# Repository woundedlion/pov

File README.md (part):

# Holosphere

[▶ Play with the live WebAssembly simulator](https://woundedlion.github.io/daydream/)

[📖 API documentation (Doxygen)](https://woundedlion.github.io/pov/)

---

<p align="center">
  
</p>

Holosphere is a persistence-of-vision (POV) LED sphere and its real-time simulator. The device spins a strip of LEDs at 480 RPM while Teensy microcontrollers fire pixels at microsecond intervals, painting full-color imagery onto the surface of a virtual sphere. The simulator compiles the same C++ effects to WebAssembly and renders them in a browser.

The project spans **two repositories** that ship as one product:

| Repo | Role | What lives here |
|---|---|---|
| [**Holosphere**](https://github.com/woundedlion/pov) | C++ engine + firmware | All rendering code, effects, hardware drivers (`pov_single.h`, `pov_segmented.h`), the Emscripten/WASM target, unit tests, and this README. |
| [**daydream**](https://github.com/woundedlion/daydream) | Web simulator | Three.js renderer, GUI and sidebar, recorder, segmented-POV Web Workers, standalone design tools, and the installed `generated/holosphere_wasm.{js,wasm}` engine build. |

Holosphere's WASM install step writes the engine module and everything the simulator mirrors from this repository into a sibling `daydream/` checkout ([§8.2](#82-wasm-build)). The live demo is daydream served from GitHub Pages.

---

## Quickstart

To explore effects, open the [live simulator](https://woundedlion.github.io/daydream/).

For local development:

1. Clone Holosphere and daydream as sibling directories.
2. Install Python with pip, Node.js with npm, CMake, Ninja and Emscripten. The tested tool versions are pinned in `tools/build_pins.py`, and each repository's `package.json` declares its Node requirement. Install the pinned host development tools with pip (including CMake and `just`):

   ```bash
   python -m pip install --require-hashes -r requirements/dev.txt
   ```

3. Install Emscripten in the sibling `../emsdk` checkout (or set `EMSDK` to its location), then build and install the engine from Holosphere:

   ```bash
   just install
   ```

4. In daydream, run `npm ci`, then `python -m http.server 8000 --bind 127.0.0.1`, and open <http://localhost:8000>.

**Troubleshooting.** The WASM recipes load the Emscripten environment automatically; check `EMSDK` if your SDK lives outside `../emsdk`. If daydream's provenance test reports a bundle mismatch, rerun `just install` to refresh the engine and its provenance together. Documentation checks need the daydream checkout at the revision pinned in `tools/build_pins.py`.

[§8 Building and Testing](#8-building-and-testing) covers native tests, firmware uploads and CI.

## Table of Contents

1. [Hardware](#1-hardware)
2. [Architecture](#2-architecture)
3. [Design Decisions](#3-design-decisions)
4. [Frame Lifecycle](#4-frame-lifecycle)
5. [Rendering](#5-rendering)
   - [5.1 Rendering Paths at a Glance](#51-rendering-paths-at-a-glance)
   - [5.2 Shared Building Blocks](#52-shared-building-blocks)
   - [5.3 Forward Rendering: Scan](#53-forward-rendering-scan)
   - [5.4 Forward Rendering: Plot](#54-forward-rendering-plot)
   - [5.5 Full-Screen Shading](#55-full-screen-shading)
   - [5.6 Pullback Shading](#56-pullback-shading)
   - [5.7 Raycasting and Raymarching](#57-raycasting-and-raymarching)
   - [5.8 The Filter Pipeline](#58-the-filter-pipeline)
6. [Effects](#6-effects)
7. [The Web Simulator (Daydream)](#7-the-web-simulator-daydream)
8. [Building and Testing](#8-building-and-testing)
9. [Repository Map](#9-repository-map)

- [License](#license)

---

## 1. Hardware

Two physical targets share the same rendering engine.

### 1.1 Holosphere (2015)

| Component | Detail |
|---|---|
| Controller | Teensy 4.0 (600 MHz ARM Cortex-M7) |
| LEDs | 40-pixel addressable strip (20 per half-arm, two-arm rotation) |
| Protocol | SPI via FastLED (WS2801 at 6 MHz) or DMA (HD107S at 12 MHz) |
| Rotation | 480 RPM (8 revolutions/second) |
| Virtual resolution | 96 × 20 |
| Driver | `POVDisplay<40, 480>` in `pov_single.h` |
| Pin assignments | DATA: pin 11, CLOCK: pin 13, RANDOM seed pin 15: legacy effects only |

### 1.2 Phantasm

| Component | Detail |
|---|---|
| Controllers | 4× Teensy 4.0 by default; optional 8× firmware profile (600 MHz ARM Cortex-M7) |
| LEDs | 288 total: 72 per segment at N=4, 36 per segment at N=8 |
| Protocol | DMA (HD107S at 24 MHz) |
| Rotation | 480 RPM (8 revolutions/second), 16 FPS from 2 sides of the ring |
| Virtual resolution | 288 × 144 |
| Driver | `POVSegmented<288, N, 480>` in `pov_segmented.h`, `N ∈ {4, 8}` (even power of two; `N=2` exceeds the per-column DMA budget at 288 px/480 RPM) |
| Synchronization | 1-wire: count-coded sync symbols from segment 0 discipline a per-board flywheel timebase (`hardware/pov_sync.h`) |
| Pin assignments | ID: pins 21–22 at N=4, plus pin 23 at N=8; Sync: rev 1.1 pin 3 (shared — master drives, downstream receive); rev 1.2 TX pin 4 via U1 (held LOW on downstream boards), RX pin 3, master-enable: pin 5, SPI: pins 11 + 13 |

### 1.3 How the Image Forms

Each revolution takes about 125 ms. The LED strip is mounted on both sides of a rotating arm: the top half of the strip paints one hemisphere and the bottom half paints the opposite one, and the two arms sit half a turn apart in azimuth. Half a revolution therefore paints a complete sphere, and each revolution delivers two frames — one per side.

A new column is painted every `1,000,000 / (RPM/60) / W` microseconds — about 1302 µs for Holosphere's 96 columns and 434 µs for Phantasm's 288. On Holosphere an IntervalTimer ISR advances one column per fire; on Phantasm each board's flywheel ISR derives the column from the CPU cycle counter ([Hardware Drivers](https://github.com/woundedlion/pov/blob/master/docs/subsystems.md#hardware-drivers-dma_ledh-pov_singleh-pov_segmentedh)).

---

## 2. Architecture

### 2.1 Layers

Firmware, WebAssembly and native test targets share one engine:

```text
C++ codebase
  effects/ (46 visual algorithms) + workbench/
              |
  core/                       Rendering engine
    scan / plot -> filter pipeline -> Canvas pixel buffer
    pullback / raycast -> Scan::Shader -> Canvas pixel buffer
              |
  targets/                    Build entry points
    Holosphere/ + Phantasm/ -> hardware/ POV and DMA drivers -> Teensy LEDs
    wasm/                  -> Emscripten -> daydream Three.js simulator
  tests/                   -> native host tests
```

- **`effects/`** holds the visual effects. Each one renders a frame into a `Canvas` using engine primitives ([§6](#6-effects)).
- **`core/`** is the engine: math, geometry, memory, color, animation, the rasterizers and shaders ([§5](#5-rendering)), and the effect control surface (parameters, presets, choreography).
- **`hardware/`** drives the LEDs: the single-board and segmented POV drivers, DMA LED controller and multi-board frame sync.
- **`targets/`** has one entry point per build: the Holosphere, Phantasm, Bench and Profile firmware sketches, the WASM bridge, and the effect rosters they register.

The engine's subsystems — shaders, rasterizers, animation, transformers, memory, color, meshes, generators, presets, math kernels, spatial queries and hardware drivers — are documented in depth in [`docs/subsystems.md`](https://github.com/woundedlion/pov/blob/master/docs/subsystems.md). Every effect is catalogued in [`docs/effects.md`](https://github.com/woundedlion/pov/blob/master/docs/effects.md).

### 2.2 Compile-Time Resolution

Resolution-dependent effects and pipeline stages are templated on `<int W, int H>`:

```cpp
template <int W, int H> class HopfFibration : public Effect { ... };
template <int W, int H, typename... Filters> struct Pipeline { ... };
```

The compiler specializes these templates for each supported resolution: `<96, 20>` for Holosphere and `<288, 144>` for Phantasm. The simulator and test suite build both. Shared interfaces such as `Canvas` and `Effect` take runtime dimensions, and resolution-independent geometry types need no template parameters.

### 2.3 Platform Abstraction

`platform.h` hides the target-specific differences:

| Symbol | Arduino/Teensy | WASM/Desktop |
|---|---|---|
| `DMAMEM` | Teensy DMA-accessible RAM segment | No-op macro |
| `hs::log()` | `Serial.println()` | `vprintf`/`printf` |
| `hs::millis()` | `::millis()` | `std::chrono` |
| `hs::rand_f()` | `Pcg32(1337)` | `Pcg32(1337)` |
| `hs::disable_interrupts()` | `noInterrupts()` | No-op |
| `CRGB`, `CHSV` | FastLED types | Struct mocks |

The host-side mocks — the `CRGB`/`CHSV` structs plus the rest of the emulated Arduino/FastLED surface (`random8`, `beatsin8`, `SerialMock`, …) — live in `platform/arduino_mocks.h`, included from `platform.h`'s non-Arduino branch.

### 2.4 Coordinate Conventions

- **Y-up Cartesian**: `Vector(x, y, z)` — `y` is the vertical axis
- **Spherical**: `theta` = azimuth (longitude), `phi` = polar angle from +Y (co-latitude)
- **Pixel mapping**: columns map to longitude; rows sample the calibrated LED-center span with `phi = north + y*(south-north)/(H-1)`.
- **Display geometry**: the LED rows do not reach the poles. Firmware uses provisional LED-center endpoints from `math/display_geometry.h`; daydream defaults to full coverage and offers Top cap (%) and Bottom cap (%) in the global controls. Both endpoint rows are latitude rings, and antialias contributions that fall in the missing rows are discarded. The ideal profile explicitly includes both poles.
- **SDF distances**: shape-specific signed distance reports. Rings and spherical primitives use angular units; PlanarPolygon, Star and Flower use chart distances. `SDF::Face` uses gnomonic tangent-plane distance for small faces and `atan` of that distance for larger faces; the latter is angular but is not a metric geodesic distance. Each shape's `size` uses its corresponding distance units.
- All geometry LUTs (`PhiLUT<H>`, `TrigLUT<W,H>`) are pre-computed eagerly via `init_geometry_luts()` at engine setup

```
   Side view (looking down −Z):          Bottom view (looking toward +Y):

         +Y (φ=0, north pole)                   +Z (θ=π/2)
          │                                      │
          │  ╱ point P                           │
          │ ╱φ                                   │  ╱ point P
          │╱                                    │ ╱θ
  ────────●────────  equator (φ=π/2)    ────────●────────  +X (θ=0)
          │                                      │
          │                                      │
         −Y (φ=π, south pole)                   −Z (θ=3π/2)

   Pixel canvas → sphere:
      x ∈ [0, W)  →  θ ∈ [0, 2π)    column wraps around the equator (x=0 at +X)
      y ∈ [0, H)  →  φ ∈ [north, south]     row 0 is the northernmost LED row
                    ideal profile [0, π]; firmware: calibrated LED span
```

---

## 3. Design Decisions

These decisions shape much of the engine, and the rest of this document assumes them.

### 3.1 Why 16-bit Linear Color?

Most LED art codebases use gamma-corrected 8-bit values throughout and blend in sRGB space. That produces muddy mixes: red + blue gives dark purple instead of magenta. Holosphere blends in linear light at 16-bit precision and packs linear 8-bit PWM with adaptive per-pixel 5-bit brightness at the HD107S hardware output. The improvement is most visible in soft gradients and multi-layer alpha compositing. Palette interpolation goes a step further, into the OKLCH perceptual color space, with shortest-arc hue interpolation that avoids the red→green→blue detour.

### 3.2 Why Compile-Time Resolution?

Templating on `<W, H>` lets the compiler fold resolution-dependent constants in coordinate transforms, bounding-box computations and LUT indexing. Values that depend on scene data are still computed at runtime. Each hardware image runs only its own specialization, so generality costs nothing at runtime; the price is binary size, because each supported resolution is a separate instantiation.

### 3.3 Why Arena Allocation?

The Teensy heap fragments under heavy mesh subdivision, so the engine avoids it: it carves a single fixed block (`GLOBAL_ARENA_SIZE`) into a persistent arena and two scratch arenas, which gives deterministic memory behavior: persistent data is allocated once and kept, and scratch data is RAII-scoped to the function that needs it.

- `configure_arenas()` lets an effect repartition the block — mesh-heavy effects claim more persistent space, subdivision-heavy effects expand their scratch pools.
- Geometry functions take explicit arenas — Conway operators take `(Arena& target, Arena& temp)`, generators take `(Arena& a, Arena& b)` — so the memory layout of heavy geometric operations is visible at every call site.
- Scratch lifetimes are LIFO: a callback allocates only under its own `ScratchScope` and never calls `reset()`, which would invalidate its caller's live buffers.

[Memory Architecture](https://github.com/woundedlion/pov/blob/master/docs/subsystems.md#memory-architecture-memoryh-memorycpp) lists the global scratch consumers and the compaction machinery.

### 3.4 Why the ISR Double Buffer?

Pixel data must be ready before each column interval fires ([§1.3](#13-how-the-image-forms)). Rendering inside the ISR would block the main loop, so the main loop renders freely into a back buffer while the ISR reads a separate front buffer. `queue_frame()` publishes the finished buffer with a release store to `next`, paired with the ISR's acquire load in `advance_display()` when adopting it. [§4](#4-frame-lifecycle) walks through the mechanics.

### 3.5 Why Fail-Fast (`HS_CHECK`)?

On an unattended board, a corrupted arena can ship garbage to the LEDs with no debugger or serial monitor to expose the cause. So invariant violations *trap at the violation site* instead of being masked by bounded fallbacks.

**How it works.** `HS_CHECK(cond, fmt, ...)` (`platform.h`) takes a mandatory condition and an optional printf-style message saying *what* went wrong — on a headless board that message is the whole post-mortem, so a bare `HS_CHECK(cond)` is the degenerate case. On failure, `hs::check_fail()` formats the message into a fixed stack buffer (no heap, so it is safe from a corrupted-arena or OOM context), logs `HS_CHECK failed: <basename>:<line> <message>` on the device, adds `(<cond>)` on host builds, **flushes** the log so a release build emits it, and calls `__builtin_trap()`. The device path uses newlib's integer-only `vsniprintf` to keep the float formatter out of ITCM. When the condition holds, the check is a single predicted-not-taken branch. Unlike `assert()` it is **not** stripped by `NDEBUG`; the device build defines `NDEBUG` only to keep newlib's `__assert_func`→`fprintf` (and all of stdio) out of the image.

**Where it goes.** `HS_CHECK` guards seams where a violation is a logic or sizing bug with no valid recovery: container growth, arena OOM, capacity and bounds guards at allocation, registration and configuration sites, and checked accessors that run per control point (such as `StaticCircularBuffer::operator[]`). It stays out of per-pixel loops, which index raw storage directly; hot paths that need a check use `HS_AUDIT_CHECK`, which traps in every host test build and compiles out on device, backed by an `HS_CHECK` at the corresponding bind or setup site. Raw `assert` is rejected in engine sources (`tests/check_death_pins.py`). The exceptions are guarded math helpers with no bind seam to carry the check — `Vector::normalized()`, `Quaternion::normalized()`, `parallel_transport()`, `angle_between()` and the polyhedral kaleidoscope lenses' unconverged-fold fallthrough — where dropping the check would turn a degenerate input into a silent NaN.

Genuinely *transient* conditions (a DMA overrun, a dropped frame) are not invariant violations and get bounded, soft handling instead. The native test suite includes a death harness that confirms reachable traps actually fire (`SIGILL` / `STATUS_ILLEGAL_INSTRUCTION`).

---

## 4. Frame Lifecycle

Every effect renders a frame inside `draw_frame()`. The `Canvas` object brackets that work, and the target decides how the finished buffer reaches the LEDs or the browser.

### 4.1 The Canvas

`Canvas` is a RAII scope guard for one frame. Constructing it acquires the next write buffer; destroying it queues the finished frame for display.

```cpp
void draw_frame() override {
    Canvas canvas(*this);   // advance_buffer() — grab write buffer
                            // clear buffer if !persist_pixels && !replaces_frame
    // ... render here using canvas(x, y) = pixel ...
}                           // ~Canvas() — queue_frame()
```

`canvas(x, y)` is a direct array subscript into the write buffer (`bufs[cur][y * width + x]`): bounds are audited (`HS_AUDIT_CHECK`) in the native test builds and unchecked in WASM and firmware builds, and there is no virtual dispatch.

The clear covers only the current display clip unless a filter declares `reads_outside_band`. Rendering a full frame and sampling old framebuffer contents outside the band are separate properties: `World::Trails` needs the former, while `Pixel::Feedback` needs both. The margin-expanded render band is otherwise write-only scratch; its width is the pipeline's `total_segment_margin` — the sum of each filter's `segment_margin` (how far the stage's output lands from the plotted position), floored at 1. Filtered effects derive all three properties from their pipelines ([§6.3](#63-the-effectconfig-flags)).

### 4.2 Hardware Path

```
Main Loop (draw_frame)                    ISR (show_col, fires every N µs)
─────────────────────────────────         ─────────────────────────────────
                                          Timer fires at column interval
POVDisplay<S,RPM>::show<Effect>()
  IntervalTimer::begin(show_col, interval)

  effect->draw_frame():
    Canvas canvas(*effect)               ISR reads from bufs[prev]
      ↓ advance_buffer()                 for y in 0..S/2:
      ↓ (copies prev if persist_pixels)    leds[S/2 - y - 1] = get_pixel(x, y)
      ↓                                    leds[S/2 + y]     = get_pixel(x±W/2, y)
    [effect renders to bufs[cur]]
      ↓                                  FastLED.show()
    ~Canvas():                           if strobe_columns(): FastLED.showColor(black)
      queue_frame()                      x = (x+1) % width
      ↓ next = cur (interrupt-safe)      if x==0 || x==width/2:
                                           advance_display()  (prev = next)
                                           [new frame begins displaying]
```

Three `std::atomic<int>` indices manage the double buffer:

| Index | Role |
|---|---|
| `cur` | Which buffer the main loop is currently writing |
| `next` | The last completed frame (queued by `queue_frame()`) |
| `prev` | The frame the ISR is currently reading |

The ISR never touches `cur`. The main loop publishes `next` with a release store in `queue_frame()`. The ISR's acquire load in `advance_display()` adopts it at every half-revolution, flipping `prev` to `next`.

Phantasm's `POVSegmented` driver follows the same double-buffer contract, but each board renders only its own segment clip and its flywheel ISR derives the column from the cycle counter.

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
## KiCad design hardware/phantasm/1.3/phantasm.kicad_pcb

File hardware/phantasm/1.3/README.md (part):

# PHANTASM rev 1.3 differential-sync design

Rev 1.3 uses RS-485 for the existing count-coded sync protocol. The electrical
review selects the components below for four boards with at most 1 m between
adjacent boards, entirely on the rotor (3 m total for three inter-board cables).
**This unrouted project has locked placement.** Mechanical review, routing,
power and harness qualification, and matching firmware are required before
fabrication. Rev 1.2 remains the generator default.

## Selected components

The schematic carries Manufacturer, MPN and Datasheet fields for the
transceiver, TVS, bus resistors, input and bulk capacitors, decouplers and
control resistors. Hand-assembled J3A and J3B carry their order code in
Value. Verify assembly-house stock, substitutions and CPL rotations.

| Reference | Manufacturer / orderable part | Selection |
|---|---|---|
| U_SYNC | Texas Instruments **THVD2410DR** | 3.3 V, SOIC-8, 500 kbps, slew-limited transceiver |
| D_SYNC | Bourns **CDSOT23-SM712** | RS-485 TVS array, SOT-23; pins 1/2 to A/B, pin 3 to GND |
| R_A, R_B | Vishay **CRCW060310R0FKEAHP** | 10 Ω, 1%, 0603, pulse-proof, 0.33 W at 70°C |
| R_TERM | Vishay **CRCW0805120RFKEAHP** | 120 Ω, 1%, 0805, pulse-proof, 0.5 W at 70°C |
| C_DEC1, C_DEC2, C_DEC3 | YAGEO **CC0603KRX7R9BB104** | 100 nF, 50 V, X7R, 10%, 0603 |
| C_BULK3 | YAGEO **CC0603KRX7R8BB105** | 1 µF, 25 V, X7R, 10%, 0603 |
| C_IN | Nichicon **UPW1H101MPD** | 100 µF, 50 V, 105°C, radial 8 × 11.5 mm, 3.5 mm lead pitch; retain mechanically |
| R_TX, R_MEN, R_DATA_PD, R_CLK_PD | YAGEO **RC0603FR-0710KL** | 10 kΩ, 1%, 0603; TX pull-up, DE and LED-input pull-downs |
| J3A, J3B | GCT **TBC05-04-1-G-G** | Four-position screw terminal; hand assembly and harness retention required |

Component references: [TI transceiver](https://www.ti.com/lit/ds/symlink/thvd2410.pdf),
[Bourns TVS](https://www.bourns.com/docs/product-datasheets/cdsot23-sm712.pdf),
[Vishay pulse resistors](https://www.vishay.com/docs/20043/crcwhpe3.pdf),
YAGEO [100 nF](https://www.yageogroup.com/download/specsheet/CC0603KRX7R9BB104),
[1 µF](https://www.yageogroup.com/download/specsheet/CC0603KRX7R8BB105), and
[10 kΩ](https://www.yageogroup.com/component-documentation/download/specsheet/RC0603FR-0710KL).
Resistor power ratings require temperature derating and suitable PCB heat spreading.

Inherited power/LED selections remain U1 **SN74AHCT125DR**, Q_REV **AO3401A**,
F1 **TLC-NSMD050**, FB **CBW321609U601T**, C_LF **CL31A226KAHNNNE**,
R_LF **RCA051R5JLF**, and R_D1/R_D2 **0805W8F330JT5E**. J1 is
**TBC05-02-1-G-G**, J2 is **TBC05-03-1-G-G**, and U_MCU is a **Teensy 4.0**.
DATA uses U1 channel B (pins 5/6), and CLK uses channel A (pins 2/3),
aligning their source resistors with J2's DATA/CLK pin order.
The inherited supplier mappings are in [the fabrication tool](../gen/fab.py);
its rev 1.1 BOM (the only revision its CLI exports) must not be used to assemble rev 1.3.
[Nichicon's C_IN selection](https://www.nichicon.com/en-us/part/upw1h101mpd/8471/)
matches the existing radial footprint; confirm its height against the rotor envelope.

## Generate

From the repository root:

```sh
python hardware/phantasm/gen/board.py --revision 1.3 --force
python hardware/phantasm/gen/pcb.py --revision 1.3 --unplaced --force --force-teensy-library
```

Open or upload this directory's matching
[schematic](phantasm.kicad_sch), [board](phantasm.kicad_pcb), and
[project](phantasm.kicad_pro), with the accompanying libraries. These are
placement inputs, not routed fabrication artifacts. Keep downloads in the
gitignored `candidates/` directory. Commit routed projects in `<rev>/routed/`
with `candidate.json` recording Quilter provenance and source hashes.
The candidate check rejects a `final/` directory.

To regenerate rev 1.2, pass `--revision 1.2` to both commands, or omit the
selector. Generating one revision does not replace the other revision's files.

## Cable trunk

Use a 120-ohm shielded twisted pair. **Belden 3106A, black jacket (color 010)**
includes a separate insulated reference-ground conductor and is the preferred
electrical selection. **Belden 3105A 010500** also has a suitable signal pair;
its reference must come from a separate insulated wire alongside the cable or
the existing common power-ground harness after the checks below. Belden 8451
is nominally 45 ohms and is not specified for this interface.

Both sync connectors carry the same four nets:

| Pin | Signal | Wiring |
|---|---|---|
| 1 | A | First conductor of the twisted pair |
| 2 | B | Second conductor of the twisted pair |
| 3 | GND | Reference conductor when fitted; heavy wires carry LED returns |
| 4 | SHIELD | Shield/drain continuity |

These are four electrical connections, not four insulated wires. A/B carry the
differential signal current. The reference bounds ground-potential differences;
the shield intercepts interference and is not a substitute for that reference.
With 3105A, use white/blue for A and blue/white for B. With 3106A, use
white/orange for A, orange/white for B and blue/white for reference GND.

To omit the separate reference wire with 3105A, all boards must retain a
low-impedance common power-ground connection, including while their positive
supplies are switched off. Leave terminal 3 empty; preserve shield continuity
on terminal 4 and bond it only at the master. Measure each A/B conductor
relative to each receiver's local ground under motor and LED disturbances.
Target -5 V to +10 V, providing 2 V headroom inside the populated TVS's
-7 V/+12 V working limits. This is an acceptance target, not a measured result.
If common ground can disconnect independently, this wiring is not qualified.
A separate reference wire also needs a fault-current review: parallel ground
paths can carry load current and must not replace the heavy returns.

[3105A](https://www.belden.com/products/cable/electronic-wire-cable/multi-pair-cable/3105a)
is 7.47 mm diameter with an 85.65 mm minimum bend radius;
[3106A](https://www.belden.com/products/cable/electronic-wire-cable/multi-pair-cable/3106a)
is 7.87 mm diameter with about a 91 mm minimum bend radius. Clamp the jacket
to the rotor structure and balance the harness. The terminal screws must not
carry the cable's centrifugal load. Electrical suitability does not establish
fit or rotational retention. The 010500 suffix specifies a black 500-foot reel,
not the required purchase quantity; obtain suitable cut lengths.

Daisy-chain master to board 1 to board 2 to board 3. Each board's two
connectors join directly by net, with a short local transceiver branch.
Intermediate boards do not retransmit pulses. A powered-down board must
leave the bus usable; unplugging its cable interrupts downstream connectivity.
The cable may follow the rotor circumference, but ends at the last board:
do not connect the last board back to the master.

JP_TERM connects the 120-ohm termination across A/B at the two physical
ends. Termination follows the cable position. JP_SHLD connects the shield
to ground at the master. Carry shield continuity through every board and
keep it separate from the reference-ground conductor.

| Strap | Master | Intermediate board | Last board |
|---|---|---|---|
| JP_TERM | Closed | Open | Closed |
| JP_SHLD | Closed | Open | Open |

The local transceiver branch has a 10 Ω, 1% pulse-proof resistor in
each conductor and a CDSOT23-SM712 protection array on the cable side.
The connectors and termination remain on the uninterrupted trunk side
of those resistors. Preserve pair symmetry and short protection return paths.

## Electrical margins

SM712 specifies +26 V/-14 V maximum clamp at 17 A. THVD2410's ±70 V bus
limits provide headroom. Any transceiver substitute must tolerate the
clamp voltage. Trace inductance, pulse energy and protection-return
impedance still need qualification. The assembled board is **not** a ±70 V
continuous-fault interface: the TVS conducts earlier. Its usable ground-offset
envelope is constrained by the TVS's -7 V/+12 V standoff despite the IC's wider
common-mode range. These ratings come from the manufacturer references above.

The two 120 Ω terminations present 60 Ω nominal. A first-order DC budget uses
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
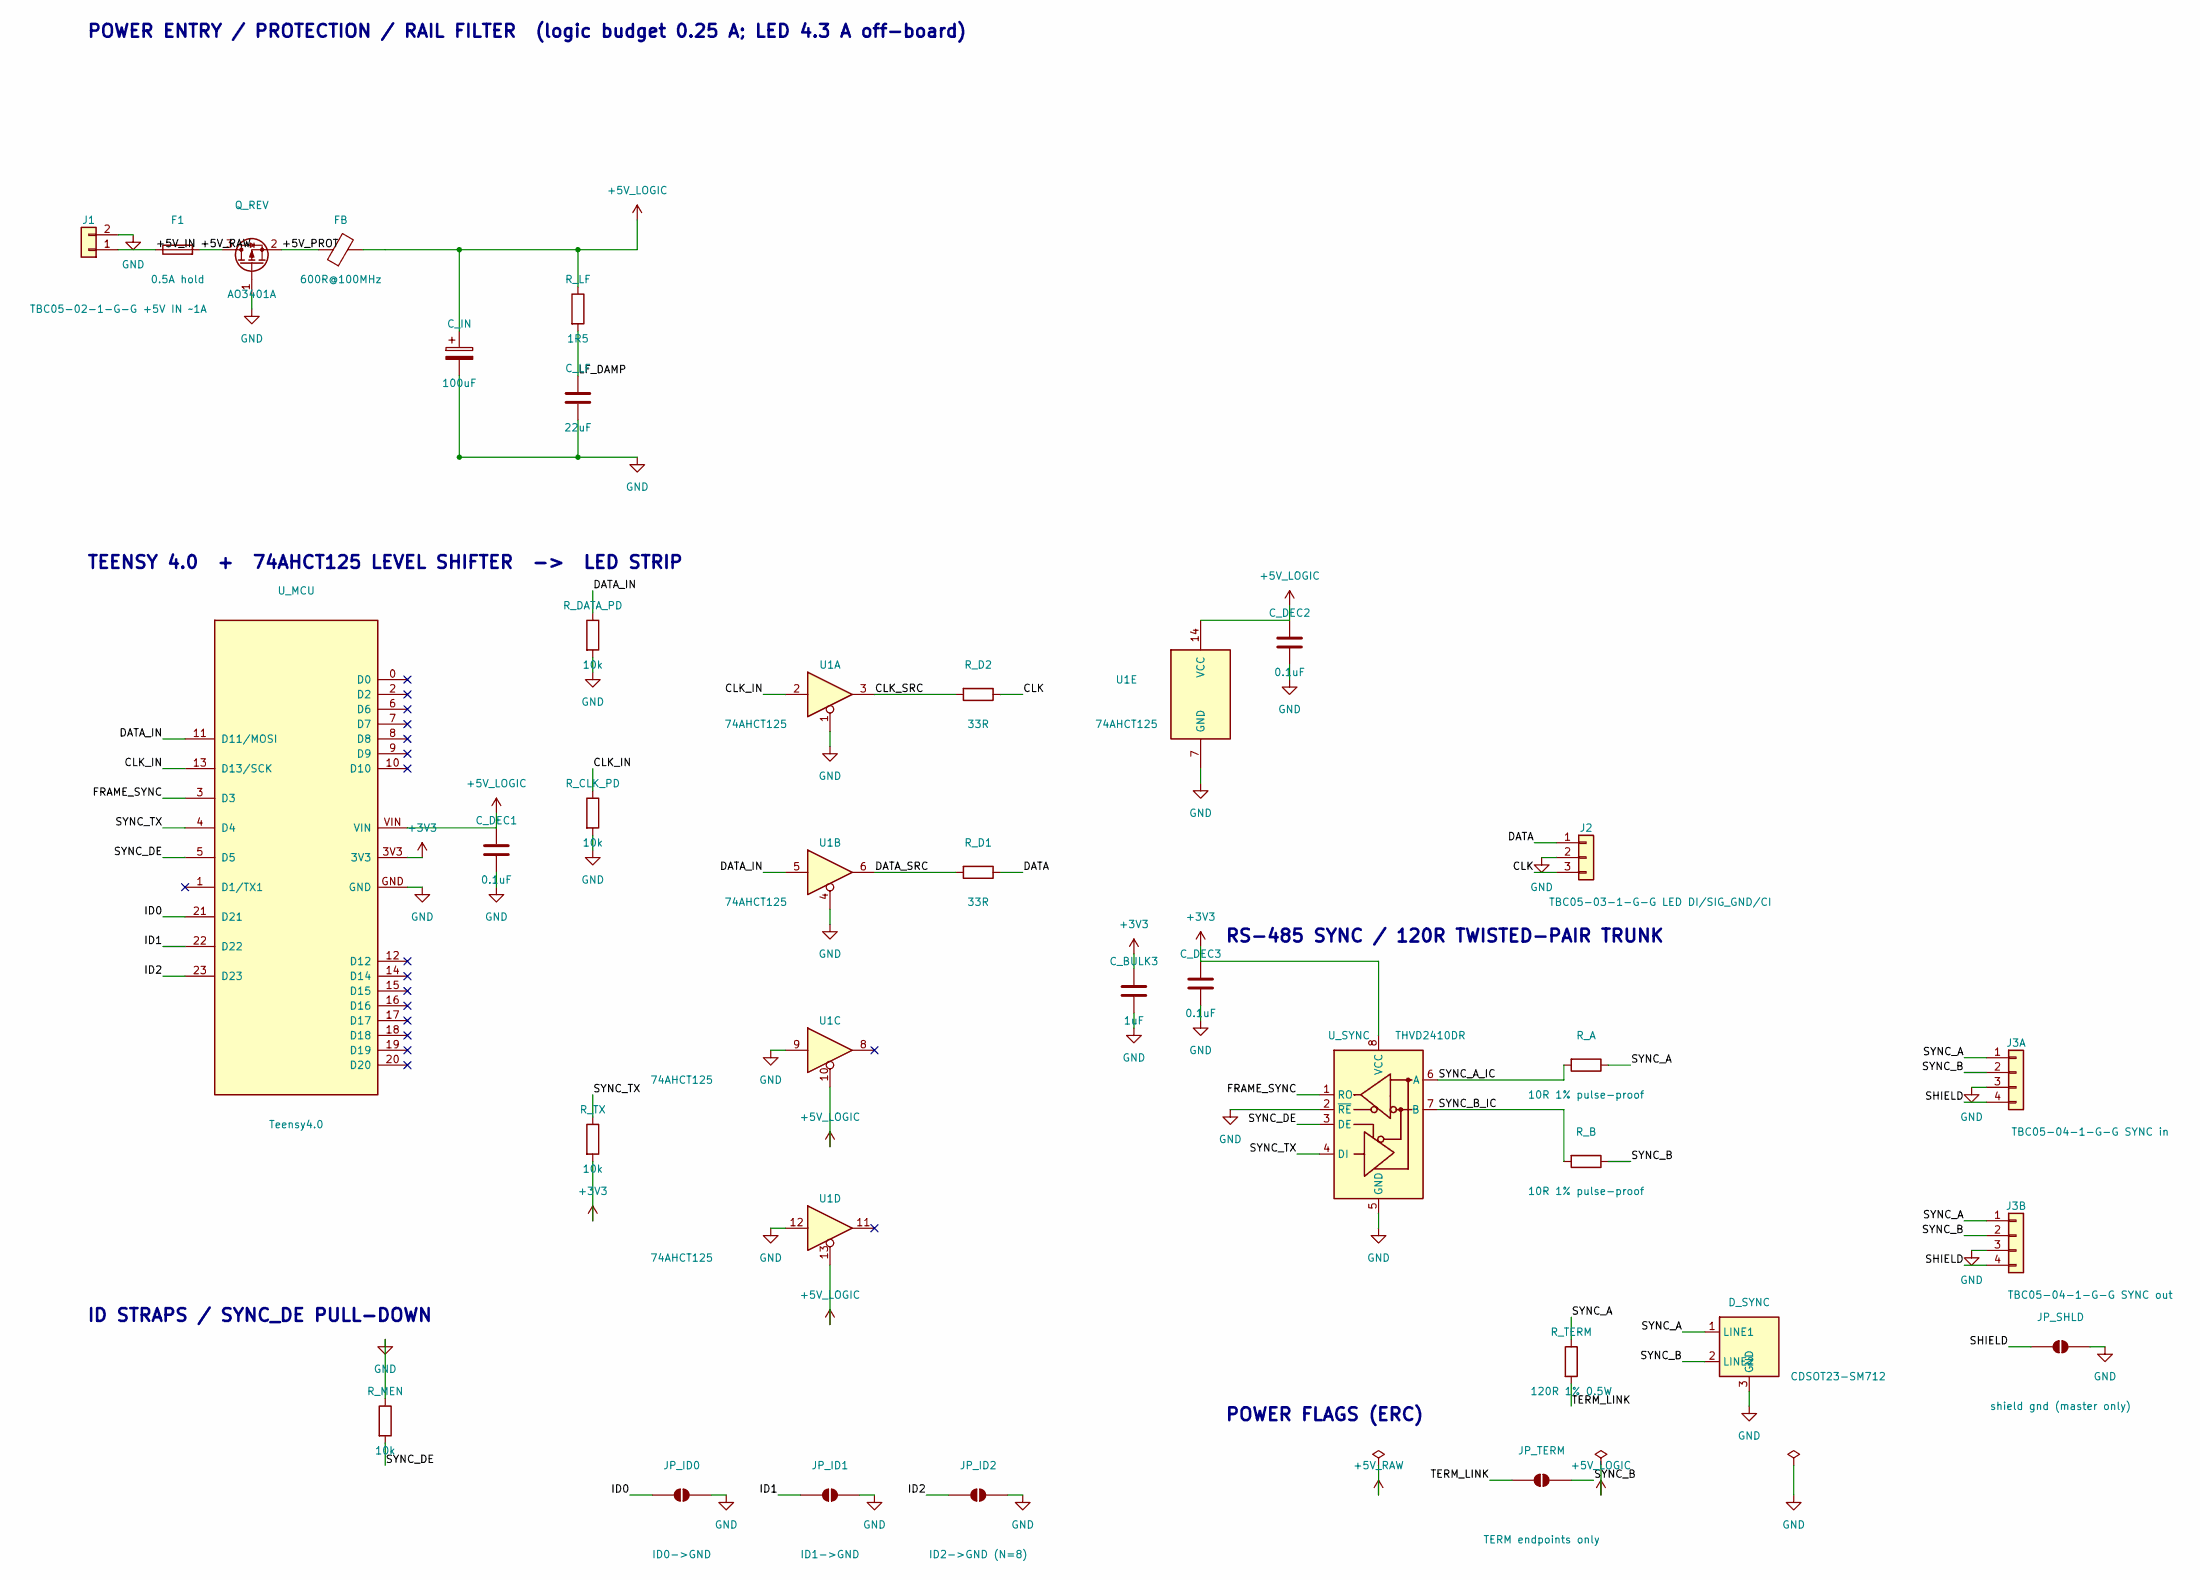
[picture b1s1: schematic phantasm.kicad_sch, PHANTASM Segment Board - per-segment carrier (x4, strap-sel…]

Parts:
C_BULK3: 1uF; C_0603_1608Metric; MPN CC0603KRX7R8BB105
C_DEC1, C_DEC2, C_DEC3: 0.1uF; C_0603_1608Metric; MPN CC0603KRX7R9BB104
C_IN: 100uF; CP_Radial_D8.0mm_P3.50mm; MPN UPW1H101MPD
C_LF: 22uF; C_1206_3216Metric
D_SYNC: CDSOT23-SM712; SOT-23; MPN CDSOT23-SM712
F1: 0.5A hold; Fuse_1206_3216Metric
FB: 600R@100MHz; L_1206_3216Metric
J1: TBC05-02-1-G-G +5V IN ~1A; TerminalBlock_GCT_TBC05-02-1-G-G
J2: TBC05-03-1-G-G LED DI/SIG_GND/CI; TerminalBlock_GCT_TBC05-03-1-G-G
J3A: TBC05-04-1-G-G SYNC in; TerminalBlock_GCT_TBC05-04-1-G-G
J3B: TBC05-04-1-G-G SYNC out; TerminalBlock_GCT_TBC05-04-1-G-G
JP_ID0: ID0->GND; SolderJumper-2_P1.3mm_Open_RoundedPad1.0x1.5mm
JP_ID1: ID1->GND; SolderJumper-2_P1.3mm_Open_RoundedPad1.0x1.5mm
JP_ID2: ID2->GND (N=8); SolderJumper-2_P1.3mm_Open_RoundedPad1.0x1.5mm
JP_SHLD: shield gnd (master only); SolderJumper-2_P1.3mm_Open_RoundedPad1.0x1.5mm
JP_TERM: TERM endpoints only; SolderJumper-2_P1.3mm_Open_RoundedPad1.0x1.5mm
Q_REV: AO3401A; SOT-23
R_A: 10R 1% pulse-proof; R_0603_1608Metric_Pad0.98x0.95mm_HandSolder; MPN CRCW060310R0FKEAHP
R_B: 10R 1% pulse-proof; R_0603_1608Metric_Pad0.98x0.95mm_HandSolder; MPN CRCW060310R0FKEAHP
R_CLK_PD: 10k; R_0603_1608Metric; MPN RC0603FR-0710KL
R_D1, R_D2: 33R; R_0805_2012Metric
R_DATA_PD: 10k; R_0603_1608Metric; MPN RC0603FR-0710KL
R_LF: 1R5; R_0805_2012Metric
R_MEN: 10k; R_0603_1608Metric; MPN RC0603FR-0710KL
R_TERM: 120R 1% 0.5W; R_0805_2012Metric_Pad1.20x1.40mm_HandSolder; MPN CRCW0805120RFKEAHP
R_TX: 10k; R_0603_1608Metric; MPN RC0603FR-0710KL
U1: 74AHCT125; SOIC-14_3.9x8.7mm_P1.27mm
U_MCU: Teensy4.0
U_SYNC: THVD2410DR; SOIC-8_3.9x4.9mm_P1.27mm; MPN THVD2410DR

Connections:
+3V3: C_BULK3.1, C_DEC3.1, R_TX.2, U_MCU.3V3, U_SYNC.8 (VCC)
+5V_LOGIC: C_DEC1.1, C_DEC2.1, C_IN.1, FB.2, R_LF.1, U1.10, U1.13, U1.14 (VCC), U_MCU.VIN
+5V_RAW: F1.2, Q_REV.3 (D)
/+5V_IN: F1.1, J1.1
/+5V_PROT: FB.1, Q_REV.2 (S)
/CLK: J2.3, R_D2.1
/CLK_IN: R_CLK_PD.1, U1.2, U_MCU.13 (D13/SCK)
/CLK_SRC: R_D2.2, U1.3
/DATA: J2.1, R_D1.1
/DATA_IN: R_DATA_PD.1, U1.5, U_MCU.11 (D11/MOSI)
/DATA_SRC: R_D1.2, U1.6
/FRAME_SYNC: U_MCU.3 (D3), U_SYNC.1 (RO)
/ID0: JP_ID0.1 (A), U_MCU.21 (D21)
/ID1: JP_ID1.1 (A), U_MCU.22 (D22)
/ID2: JP_ID2.1 (A), U_MCU.23 (D23)
/LF_DAMP: C_LF.1, R_LF.2
/SHIELD: J3A.4, J3B.4, JP_SHLD.1 (A)
/SYNC_A: D_SYNC.1 (LINE1), J3A.1, J3B.1, R_A.1, R_TERM.1
/SYNC_A_IC: R_A.2, U_SYNC.6 (A)
/SYNC_B: D_SYNC.2 (LINE2), J3A.2, J3B.2, JP_TERM.2 (B), R_B.1
/SYNC_B_IC: R_B.2, U_SYNC.7 (B)
/SYNC_DE: R_MEN.2, U_MCU.5 (D5), U_SYNC.3 (DE)
/SYNC_TX: R_TX.1, U_MCU.4 (D4), U_SYNC.4 (DI)
/TERM_LINK: JP_TERM.1 (A), R_TERM.2
GND: C_BULK3.2, C_DEC1.2, C_DEC2.2, C_DEC3.2, C_IN.2, C_LF.2, D_SYNC.3 (GND), J1.2, J2.2, J3A.3, J3B.3, JP_ID0.2 (B), JP_ID1.2 (B), JP_ID2.2 (B), JP_SHLD.2 (B), Q_REV.1 (G), R_CLK_PD.2, R_DATA_PD.2, R_MEN.1, U1.1, U1.4, U1.7 (GND), U1.9, U1.12, U_MCU.GND, U_SYNC.2 (~RE), U_SYNC.5 (GND)

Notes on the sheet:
POWER ENTRY / PROTECTION / RAIL FILTER (logic budget 0.25 A; LED 4.3 A off-board)
TEENSY 4.0 + 74AHCT125 LEVEL SHIFTER -> LED STRIP
RS-485 SYNC / 120R TWISTED-PAIR TRUNK
ID STRAPS / SYNC_DE PULL-DOWN
POWER FLAGS (ERC)

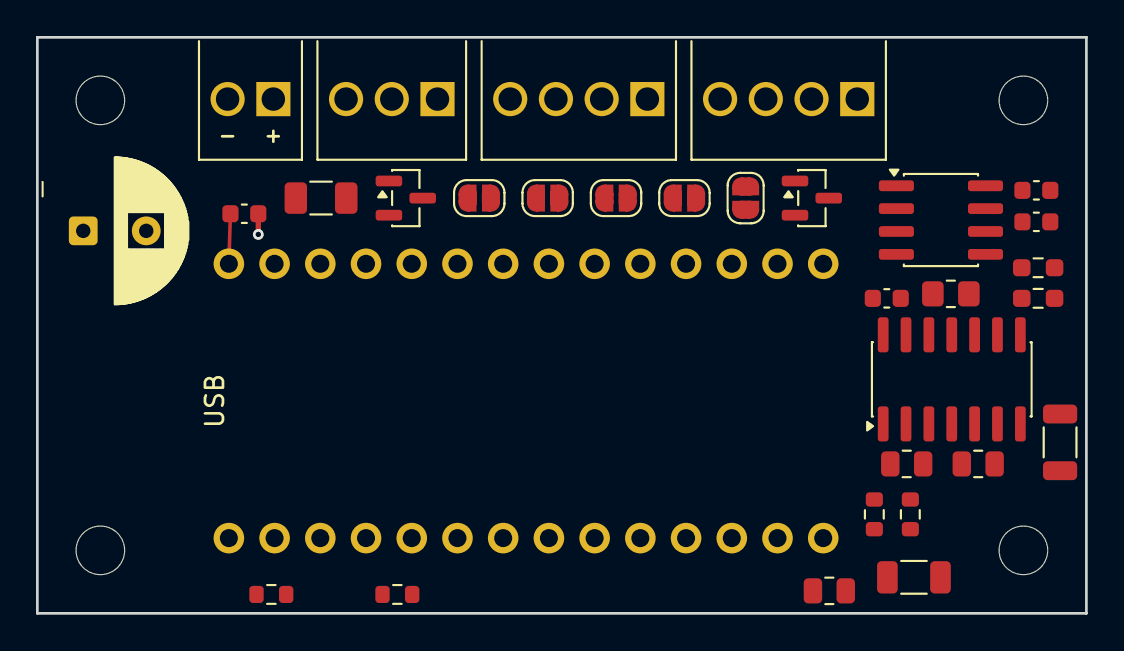
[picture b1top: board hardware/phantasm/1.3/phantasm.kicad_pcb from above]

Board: 4 copper layers, 58.3 x 32.0 mm, 36 parts (0 on the bottom side), 25 nets.

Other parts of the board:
H1, H2, H3, H4: M2.5; MountingHole_2.7mm_M2.5

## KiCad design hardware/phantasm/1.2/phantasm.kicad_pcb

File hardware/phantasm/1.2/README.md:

# PHANTASM rev 1.2 board project

Rev 1.2 is the generator default. The [board index](../README.md) covers shared generation and [release validation](../README.md#validation-and-release).

## Quilter upload

Upload these three files together from this directory:

- [phantasm.kicad_pcb](phantasm.kicad_pcb): unplaced rev 1.2 board.
- [phantasm.kicad_sch](phantasm.kicad_sch): matching rev 1.2 schematic.
- [phantasm.kicad_pro](phantasm.kicad_pro): placement and design rules.

Keep the accompanying symbol and footprint libraries with the project when
opening it in KiCad 10. Every upload must use the board and schematic from the
same revision directory. Rev 1.2 requires placement, routing, and validation
before fabrication.

The rev 1.2 upload board fixes **J1 power at the left edge** and **J2 LED, J3A SYNC IN,
J3B SYNC OUT in a column at the right end**, in that top-to-bottom order.
The column sits inboard of the right mounting holes, in the rev 1.1 connector
area. Their wire openings face left toward the hub. Keepouts reserve each
terminal's full plastic body plus 0.5 mm assembly clearance, preventing SMD
parts beneath the connector. Power's wire-access reservation extends off the
left edge. The outline remains **58.28 x 32 mm**, and all four mounting holes
retain the rev 1.1 coordinates. The Teensy shifts 3.5 mm left to clear the
terminal bodies; D_BUS is released for placement outside their keepouts.

Rev 1.2 J2/J3A/J3B have no wire-access reservation. Their openings sit
about 1.5 mm from the Teensy PCB edge; J2.1 faces a header pin that remains
in its insertion path at any socket height. Trial-fit its harness before
fabrication. Placement and DRC do not qualify harness insertion. A connector whose pin
legend meets a mounting reserve has its complete legend on the back; rev 1.2
J2 and J3B use the back, while J3A retains its complete front legend.

Rev 1.2 omits the J4 debug header and SERIAL1_TX connection; Teensy pin 1 is
unconnected. R_MEN and MASTER_EN remain part of the sync control circuit.
Probe power directly at the Teensy; diagnostics use its USB connector.

Replace the uploaded files in Quilter with this complete revision pair and
confirm all four connectors appear inside the outline as pre-placed parts.
[Quilter preserves their positions and rotations](https://docs.quilter.ai/design-parameters/pre-placed-components).
Existing routed candidates do not acquire these constraints retroactively.

The rev 1.2 schematic wires C_DEC1 directly to U_MCU VIN and C_DEC2 directly to U1 pin 14
to make their bypass assignments explicit. Both are 100 nF and preplaced on the
PCB. [Quilter prioritizes direct schematic wires when assigning bypass capacitors](https://docs.quilter.ai/placement-constraints/bypass-capacitors).
Start a fresh job to redetect the constraints; replacing files can retain an
existing incorrect assignment. Verify these two rows before submitting.

The rev 1.2 bypass table must contain only those two decouplers; remove C_IN
(bulk storage), C_LF (filter damping), and C_SYNC (signal filtering) from that
table. In Power Nets, keep 500 mA sizing for all five detected supply nets and
turn off **Attempt Power Pour** for each. These are Quilter job settings;
there is no documented KiCad property to import these exclusions or pour flags.
After correcting the job, duplicate it to reuse its design parameters and
physics constraints for subsequent runs.

In Quilter, preserve the uploaded four-layer stackup and select **Preserve copper
on internal layers**. Also add **GND plane In1.Cu** and **GND plane In2.Cu**
by name to the job's **Preserved Pours** table. Quilter deletes and regenerates
pours absent from that table; preserving an internal pour also requires preserving
the stackup. See [Quilter's preserved-pour setup](https://docs.quilter.ai/design-parameters/preserved-pours).
The board's schematic links identify related components.

The stackup is **Signal / GND / GND / Signal**. Both inner layers have GND
pours and the user names `GND` and `Ground`, matching
[Quilter's ground-layer naming rules](https://docs.quilter.ai/using-quilter/prepare-your-input-board-file).
Confirm both inner layers are classified as Ground in Quilter's stackup editor.
Its no-power-layer info is expected: this design uses two ground reference
planes, with the supply rails routed on the outer layers.

## Hardware and firmware

Rev 1.2 selects **ENIG** copper finish; the shipped rev 1.1 board uses
**Lead-Free HASL**. This is a revision-specific fabrication change.

### Terminal-block clearance

The generator uses **GCT TBC05-02-1-G-G** for J1 (board power) and
**TBC05-03-1-G-G** for J2 (LED signals), J3A and J3B (sync). J4 is absent from rev 1.2.
The [GCT mechanical drawing](https://www.farnell.com/cad/4513152.pdf) specifies
2.54 mm pitch, 1.3 mm PCB holes, and bodies **5.48 × 6.5 mm** (two positions)
or **8.02 × 6.5 mm** (three positions), 8.5 mm high.

Each terminal footprint reserves its body plus 0.5 mm on every side with a
front courtyard and a footprint-local component keepout. Traces, vias and
copper pours remain allowed beneath the plastic body. The placed draft packs
against the larger reservation; the unplaced output locks these connectors
at `TERMINAL_EDGE_PLACEMENTS`. Recheck
wire entry, screw access and rotor clearance after placement.

The committed rev 1.1 boards still carry pin-header footprints. Matching pin
pitch alone does not establish body or drill clearance for these terminals.
J1 remains pin 1 = +5 V, pin 2 = GND; the terminal block is not polarized.

### Sync circuit

Every master and follower uses the same PCB, populated parts, and pin map.
The ID straps select the role; `MASTER_EN` still gates both U1 channels C/D.

| Signal | Connections | Master | Follower |
|---|---|---|---|
| `FRAME_SYNC` | Teensy D3, R1/R2 divider, C_SYNC 220 pF | Receive-only, echo ignored | Receive with pad hysteresis |
| `SYNC_TX` | Teensy D4, U1 pin 9, R_TX 10 kΩ to GND | Sync pulse output | Output held LOW |
| `MASTER_EN` | Teensy D5, U1 pins 10/13, R_MEN pull-up | LOW after TX initialization | HIGH |

`R_TX` is populated on **every board**, including the master. It holds the AHCT
input LOW during reset while the GPIO is high impedance. The receive RC no
longer loads an AHCT input. `R_TX` uses the same 0603 10 kΩ catalog part as
`R_MEN` (C25804).

Rev 1.2 also closes rev 1.1's power-up feedback path. R_MEN pulls `/OE` to the
Teensy's 3V3 rail, which can rise after U1's 5 V supply; it cannot guarantee a
disabled driver throughout power-up. On rev 1.1 the briefly enabled receive-to-
transmit path can re-drive SYNC_BUS. Rev 1.2's separate SYNC_TX input and R_TX
hold its input LOW during that interval. This protection requires the revised
copper and firmware described below; the generator alone does not retrofit it.

**Firmware compatibility:** `HS_PHANTASM_BOARD_REV` comes from
`[phantasm_common] board_revision` in `platformio.ini`, which defaults to `11`.
Build rev 1.2 with `pio run -e phantasm_rev12`, or set `board_revision = 12`
for all Phantasm environments. The rev 1.2 pin map transmits on D4, configures
D3 as input with HYS, and initializes D4 LOW as an output on every board before
enabling the master. Followers keep D4 LOW; only the master emits pulses.
Regenerating the board does not change the firmware build flags or routed copper.

Generating rev 1.2 requires regenerating the schematic before either PCB draft.
The resulting PCB is unrouted and needs placement/routing validation before
fabrication; changing its revision label alone does not convert rev 1.1 copper.

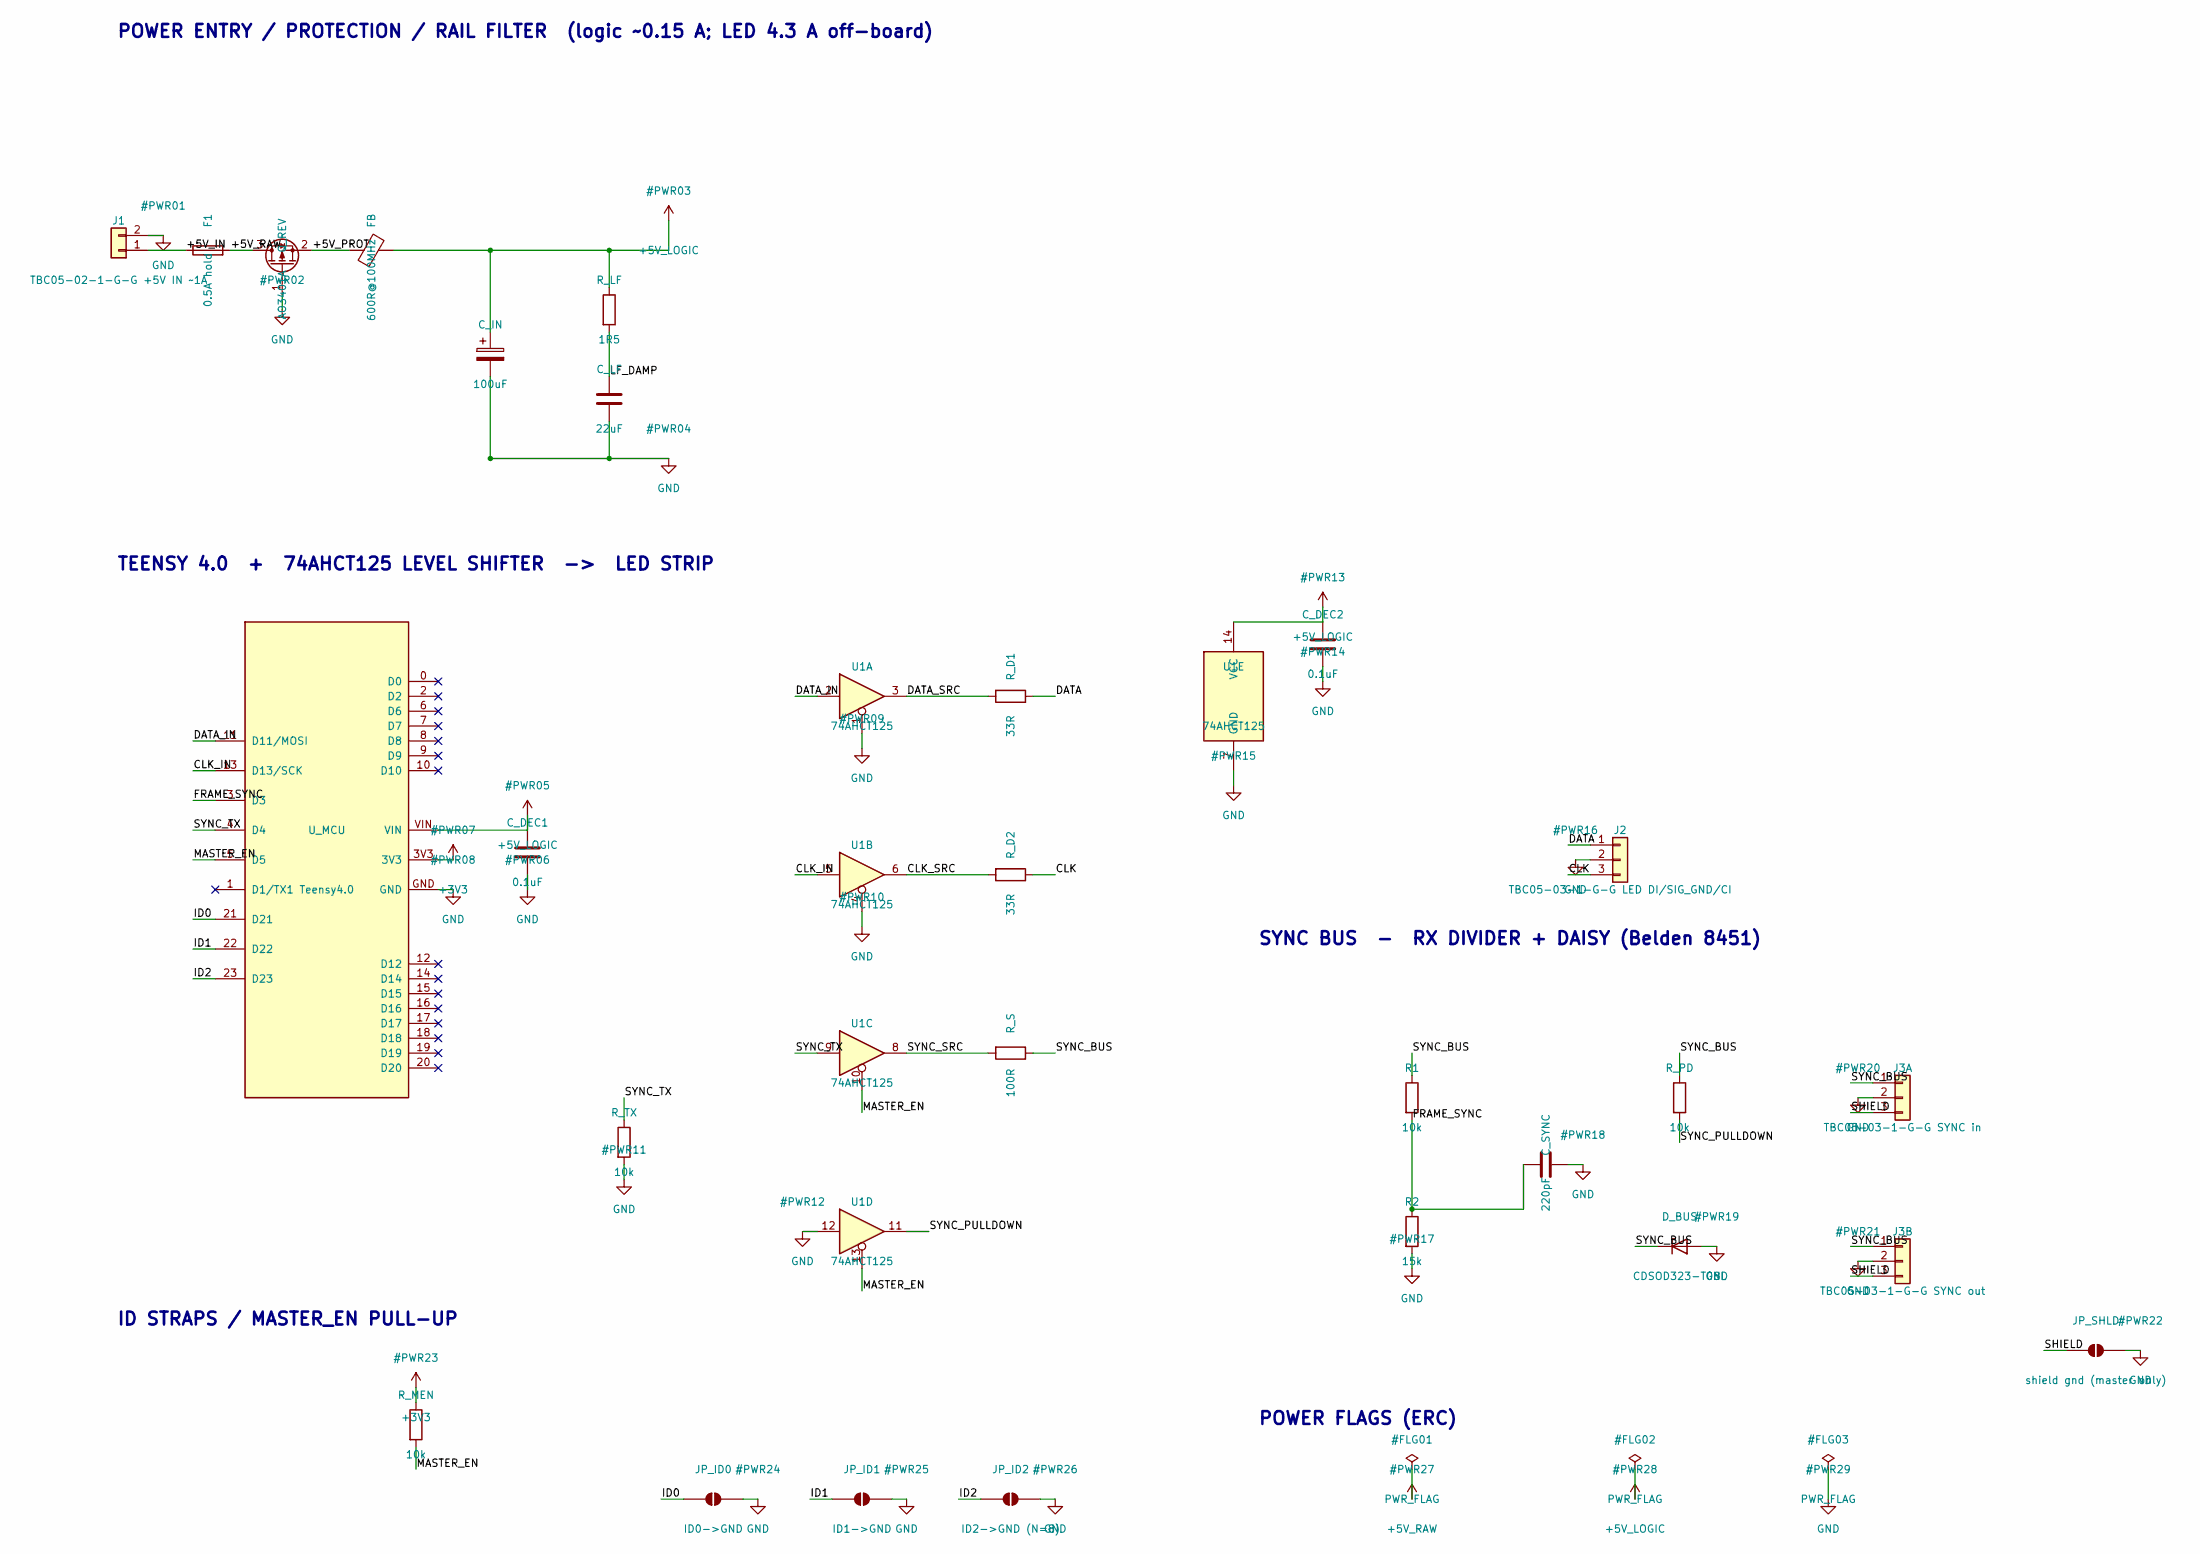
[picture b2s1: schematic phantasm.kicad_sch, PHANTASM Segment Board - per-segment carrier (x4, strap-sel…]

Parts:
C_DEC1, C_DEC2: 0.1uF; C_0603_1608Metric
C_IN: 100uF; CP_Radial_D8.0mm_P3.50mm
C_LF: 22uF; C_1206_3216Metric
C_SYNC: 220pF; C_0603_1608Metric
D_BUS: CDSOD323-T08L; D_SOD-323
F1: 0.5A hold; Fuse_1206_3216Metric
FB: 600R@100MHz; L_1206_3216Metric
J1: TBC05-02-1-G-G +5V IN ~1A; TerminalBlock_GCT_TBC05-02-1-G-G
J2: TBC05-03-1-G-G LED DI/SIG_GND/CI; TerminalBlock_GCT_TBC05-03-1-G-G
J3A: TBC05-03-1-G-G SYNC in; TerminalBlock_GCT_TBC05-03-1-G-G
J3B: TBC05-03-1-G-G SYNC out; TerminalBlock_GCT_TBC05-03-1-G-G
JP_ID0: ID0->GND; SolderJumper-2_P1.3mm_Open_RoundedPad1.0x1.5mm
JP_ID1: ID1->GND; SolderJumper-2_P1.3mm_Open_RoundedPad1.0x1.5mm
JP_ID2: ID2->GND (N=8); SolderJumper-2_P1.3mm_Open_RoundedPad1.0x1.5mm
JP_SHLD: shield gnd (master only); SolderJumper-2_P1.3mm_Open_RoundedPad1.0x1.5mm
Q_REV: AO3401A; SOT-23
R1: 10k; R_0603_1608Metric_Pad0.98x0.95mm_HandSolder
R2: 15k; R_0603_1608Metric_Pad0.98x0.95mm_HandSolder
R_D1, R_D2: 33R; R_0805_2012Metric
R_LF: 1R5; R_0805_2012Metric
R_MEN: 10k; R_0603_1608Metric
R_PD: 10k; R_0603_1608Metric_Pad0.98x0.95mm_HandSolder
R_S: 100R; R_0805_2012Metric_Pad1.20x1.40mm_HandSolder
R_TX: 10k; R_0603_1608Metric
U1: 74AHCT125; SOIC-14_3.9x8.7mm_P1.27mm
U_MCU: Teensy4.0

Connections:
+3V3: R_MEN.1, U_MCU.3V3
+5V_LOGIC: C_DEC1.1, C_DEC2.1, C_IN.1, FB.2, R_LF.1, U1.14 (VCC), U_MCU.VIN
+5V_RAW: F1.2, Q_REV.3 (D)
/+5V_IN: F1.1, J1.1
/+5V_PROT: FB.1, Q_REV.2 (S)
/CLK: J2.3, R_D2.1
/CLK_IN: U1.5, U_MCU.13 (D13/SCK)
/CLK_SRC: R_D2.2, U1.6
/DATA: J2.1, R_D1.1
/DATA_IN: U1.2, U_MCU.11 (D11/MOSI)
/DATA_SRC: R_D1.2, U1.3
/FRAME_SYNC: C_SYNC.1, R1.2, R2.1, U_MCU.3 (D3)
/ID0: JP_ID0.1 (A), U_MCU.21 (D21)
/ID1: JP_ID1.1 (A), U_MCU.22 (D22)
/ID2: JP_ID2.1 (A), U_MCU.23 (D23)
/LF_DAMP: C_LF.1, R_LF.2
/MASTER_EN: R_MEN.2, U1.10, U1.13, U_MCU.5 (D5)
/SHIELD: J3A.3, J3B.3, JP_SHLD.1 (A)
/SYNC_BUS: D_BUS.1 (K), J3A.1, J3B.1, R1.1, R_PD.1, R_S.1
/SYNC_PULLDOWN: R_PD.2, U1.11
/SYNC_SRC: R_S.2, U1.8
/SYNC_TX: R_TX.1, U1.9, U_MCU.4 (D4)
GND: C_DEC1.2, C_DEC2.2, C_IN.2, C_LF.2, C_SYNC.2, D_BUS.2 (A), J1.2, J2.2, J3A.2, J3B.2, JP_ID0.2 (B), JP_ID1.2 (B), JP_ID2.2 (B), JP_SHLD.2 (B), Q_REV.1 (G), R2.2, R_TX.2, U1.1, U1.4, U1.7 (GND), U1.12, U_MCU.GND

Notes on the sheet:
POWER ENTRY / PROTECTION / RAIL FILTER (logic ~0.15 A; LED 4.3 A off-board)
TEENSY 4.0 + 74AHCT125 LEVEL SHIFTER -> LED STRIP
SYNC BUS - RX DIVIDER + DAISY (Belden 8451)
ID STRAPS / MASTER_EN PULL-UP
POWER FLAGS (ERC)

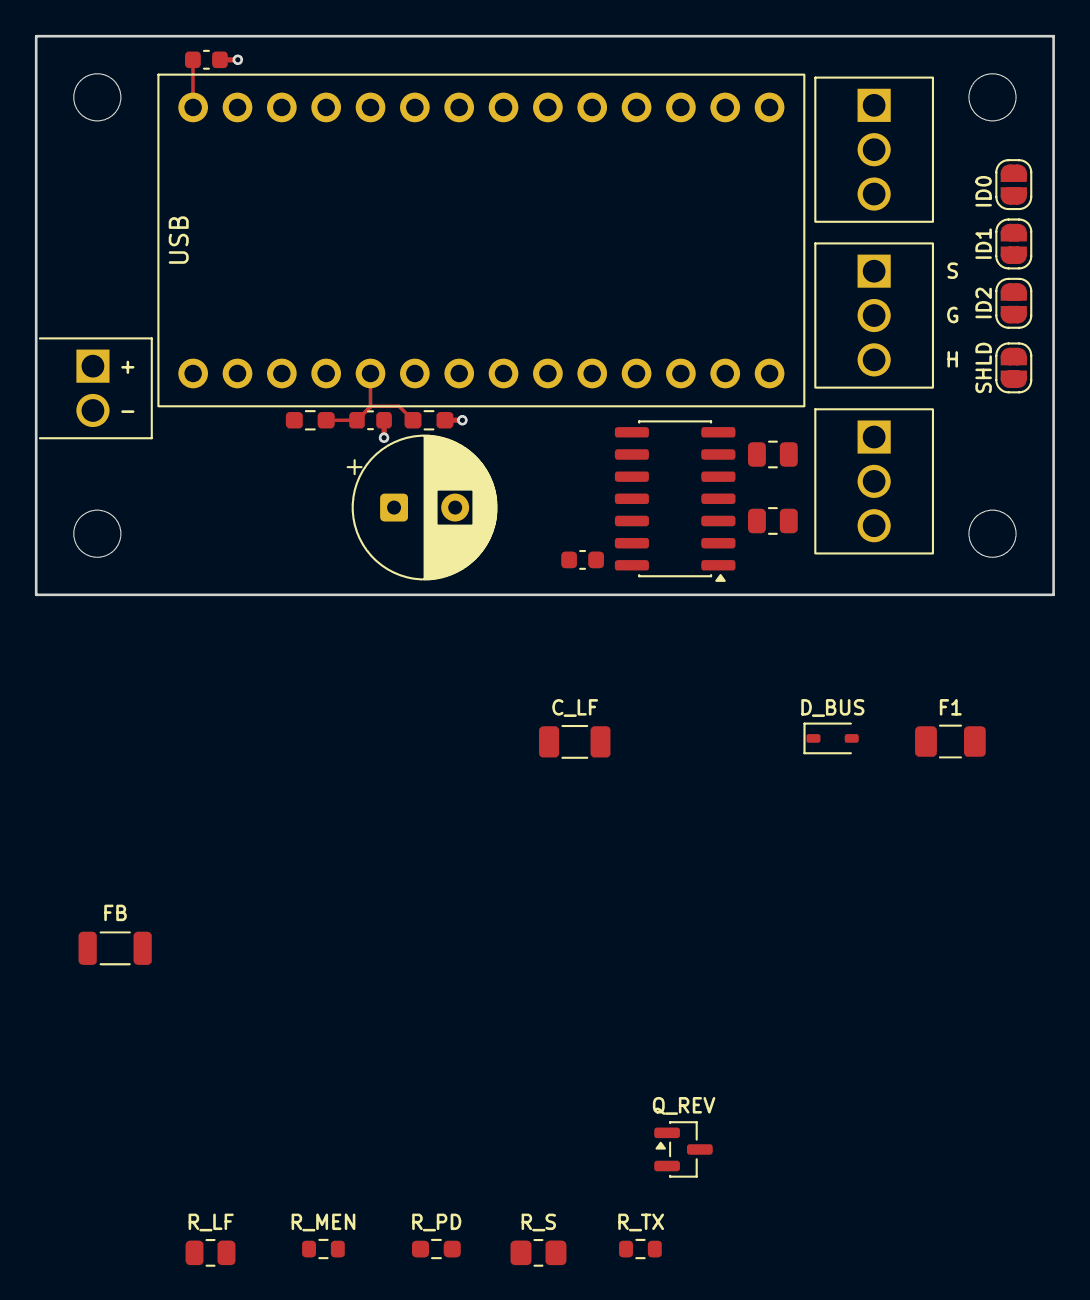
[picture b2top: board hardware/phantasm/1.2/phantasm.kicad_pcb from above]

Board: 4 copper layers, 58.3 x 32.0 mm, 32 parts (0 on the bottom side), 23 nets.

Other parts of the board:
H1, H2, H3, H4: M2.5; MountingHole_2.7mm_M2.5

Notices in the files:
README.md:
This project is split-licensed: the rendering engine and the visual effects carry different terms.
Engine and workbench — non-commercial.** The core infrastructure — the rendering engine, math, scan/raster, hardware drivers, test harness, and shader workbench, which in the Holosphere repository is everything outside `effects/` and `core/engine/effects_legacy.h` — is licensed under the [PolyForm Noncommercial License 1.0.0](https://polyformproject.org/licenses/noncommercial/1.0.0/) (see [`LICENSE`](https://github.com/woundedlion/pov/blob/master/LICENSE)). You may use, modify, and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
